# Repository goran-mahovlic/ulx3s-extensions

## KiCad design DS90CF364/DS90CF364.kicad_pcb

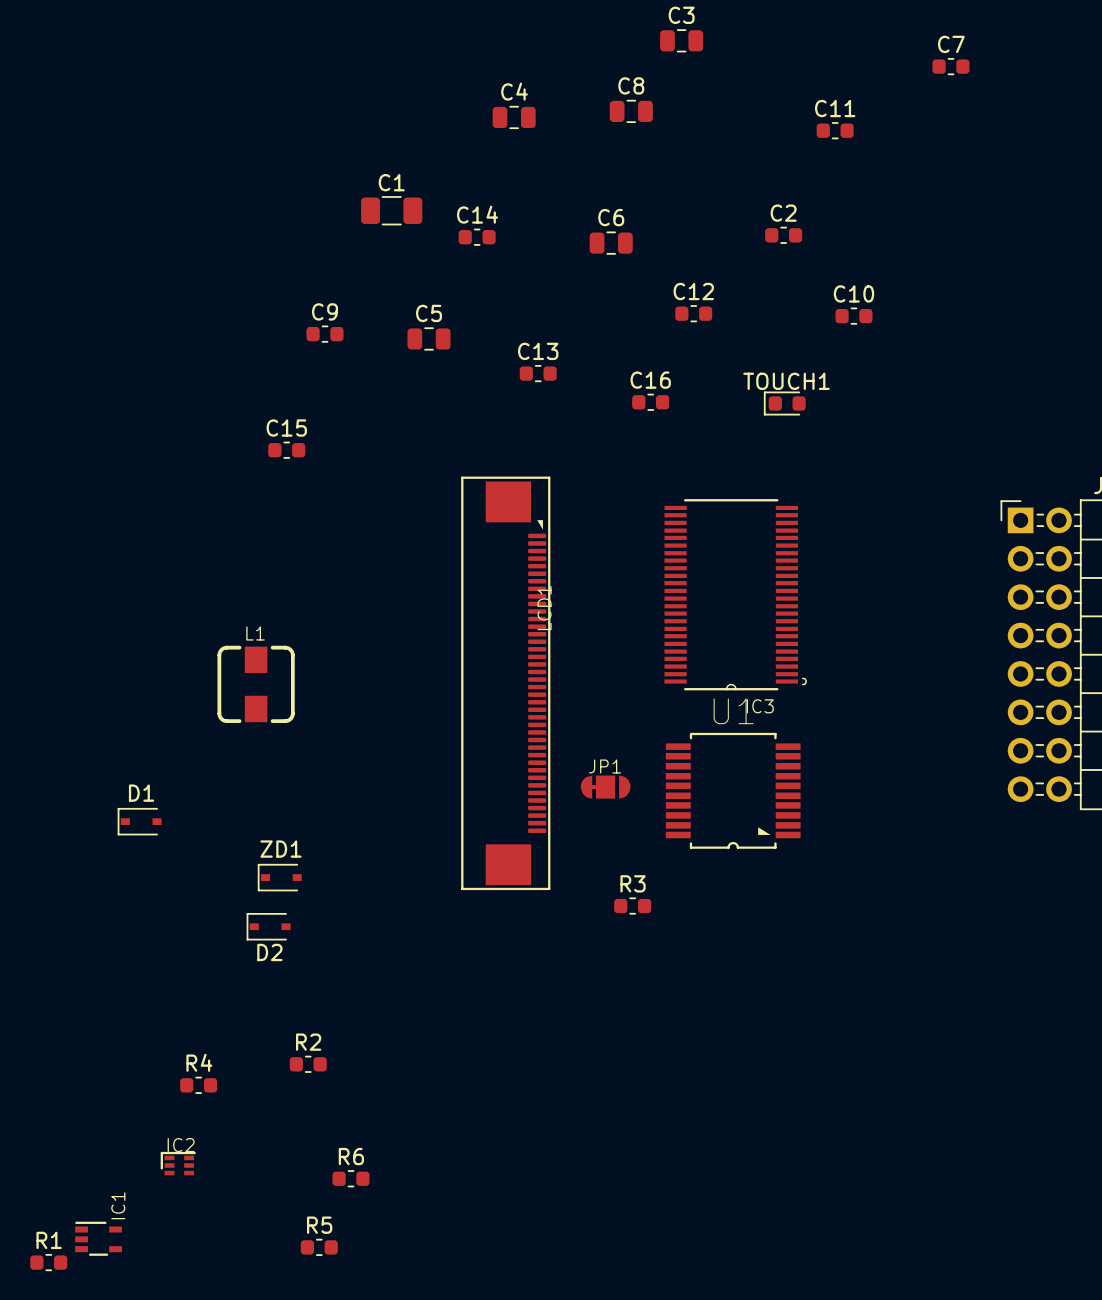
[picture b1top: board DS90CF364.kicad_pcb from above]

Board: 2 copper layers, 34 parts (0 on the bottom side), 42 nets, no tracks yet.

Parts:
C1: 4u7; C_1206_3216Metric
C2, C7, C9, C10, C11, C12, C13, C14, C15, C16: 100n; C_0603_1608Metric
C3, C8: 1u; C_0805_2012Metric
C4, C6: 10n; C_0805_2012Metric
C5: 2u2; C_0805_2012Metric
D1: D_Schottky; D_SOD-323
D2: D_Zener; D_SOD-323
IC1: TPS61169DCKR; DCK5
IC2: TPD4E001DRLR; DRL6
IC3: AR1021-I/SS; SOP65P780X200-20N
J1: Conn_02x08_Odd_Even; PinHeader_2x08_P2.54mm_Horizontal
JP1: JP3-CUT
L1: DLG-0403-4R7; DE0403
LCD1: PCA-6-LA-40-HL-3; FPC_40
R1, R2: 10R; R_0603_1608Metric
R3: 10K; R_0603_1608Metric
R4: 20K; R_0603_1608Metric
R5: 4K7; R_0603_1608Metric
R6: 1K; R_0603_1608Metric
TOUCH1: LED; LED_0603_1608Metric
U1: DS90CF364AMTD; SOP50P800X110-48N
ZD1: BZX384-B30.115; D_SOD-323

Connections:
3V3: C1.1, C2.2, C5.1, C7.2, C8.2, C9.1, C10.1, C11.1, C12.1, C13.1, C14.1, C15.1, C16.1, IC2.6, IC3.1, J1.1, J1.2, L1.1, LCD1.4, R1.1, R3.2, R6.2, U1.12, U1.20, U1.28, U1.36, U1.42, U1.48
/LCD_DISP: LCD1.31, R3.1
/LTDC_CLK: LCD1.30, U1.23
/LTDC_DE: LCD1.34, U1.5
/LTDC_HSYNC: LCD1.32, U1.2
/LTDC_RESET: JP1.COM, LCD1.36
/LTDC_VSYNC: LCD1.33, U1.4
/Touch_XL: C6.1, IC2.4, IC3.19, LCD1.39, R4.2
/Touch_XR: IC2.1, IC3.18, LCD1.37
/Touch_YD: C4.1, IC2.2, IC3.16, LCD1.38
/Touch_YU: IC2.5, IC3.15, LCD1.40
/VLED_SW: D1.2, IC1.1, L1.2
GN4: IC3.11, J1.13
GN5: IC3.9, J1.15
GND: C1.2, C2.1, C3.2, C4.2, C5.2, C6.2, C7.1, C8.1, C9.2, C10.2, C11.2, C12.2, C13.2, C14.2, C15.2, C16.2, IC1.2, IC2.3, IC3.2, IC3.3, IC3.4, IC3.7, IC3.14, IC3.17, IC3.20, J1.3, J1.4, JP1.NO, LCD1.3, LCD1.5, LCD1.6, LCD1.13, LCD1.14, LCD1.21, LCD1.22, LCD1.29, R2.2, TOUCH1.1, U1.3, U1.7, U1.13, U1.18, U1.19, U1.21, U1.25, U1.32, U1.38, U1.44
GP4: IC3.13, J1.14
GP5: IC1.4, J1.16
LTDC_B2: LCD1.23, U1.41
LTDC_B3: LCD1.24, U1.43
LTDC_B4: LCD1.25, U1.45
LTDC_B5: LCD1.26, U1.46
LTDC_B6: LCD1.27, U1.47
LTDC_B7: LCD1.28, U1.1
LTDC_G2: LCD1.15, U1.33
LTDC_G3: LCD1.16, U1.34
LTDC_G4: LCD1.17, U1.35
LTDC_G5: LCD1.18, U1.37
LTDC_G6: LCD1.19, U1.39
LTDC_G7: LCD1.20, U1.40
LTDC_R2: LCD1.7, U1.24
LTDC_R3: LCD1.8, U1.26
LTDC_R4: LCD1.9, U1.27
LTDC_R5: LCD1.10, U1.29
LTDC_R6: LCD1.11, U1.30
LTDC_R7: LCD1.12, U1.31
unnamed: IC1.5, R1.2
unnamed: IC3.5, R4.1
unnamed: IC3.6, R5.2
unnamed: R5.1, TOUCH1.2
unnamed: R6.1, U1.22
VLED+: C3.1, D1.1, D2.1, LCD1.2
VLED-: D2.2, IC1.3, LCD1.1, R2.1

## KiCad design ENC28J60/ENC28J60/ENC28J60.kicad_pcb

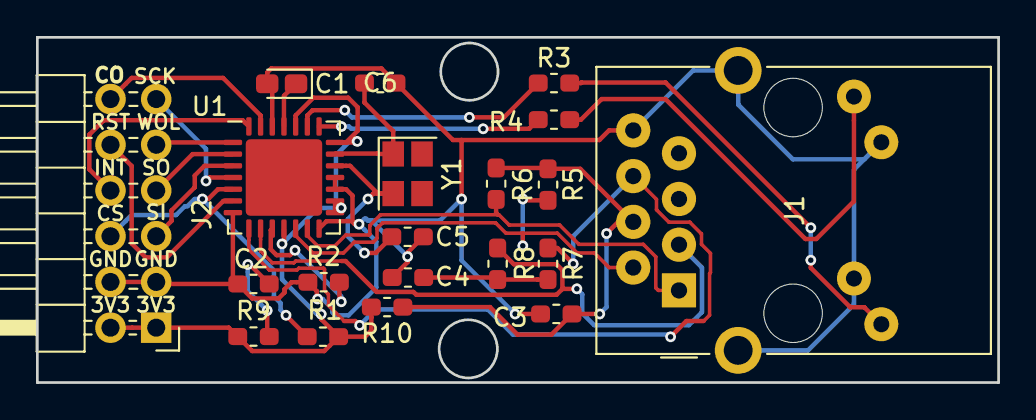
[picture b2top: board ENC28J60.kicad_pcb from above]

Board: 2 copper layers, 53.4 x 19.2 mm, 20 parts (0 on the bottom side), 25 nets.

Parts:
C1: 10u; CP_EIA-1608-08_AVX-J_Pad1.25x1.05mm_HandSolder
C2, C3, C4: 100n; C_0603_1608Metric_Pad1.05x0.95mm_HandSolder
C5, C6: 18p; C_0603_1608Metric_Pad1.05x0.95mm_HandSolder
J1: RJ45; RJ45_Amphenol_RJMG1BD3B8K1ANR
J2: Conn_02x06_Odd_Even; PinHeader_2x06_P2.54mm_Horizontal
R1, R9: 4K7; R_0603_1608Metric_Pad1.05x0.95mm_HandSolder
R2: 2K7; R_0603_1608Metric_Pad1.05x0.95mm_HandSolder
R3, R4, R5, R6, R7, R8: 270R; R_0603_1608Metric_Pad1.05x0.95mm_HandSolder
R10: 10R; R_0603_1608Metric_Pad1.05x0.95mm_HandSolder
U1: ENC28J60; QFN-28-1EP_6x6mm_P0.65mm_EP4.25x4.25mm
Y1: Crystal; Crystal_SMD_SeikoEpson_FA238-4Pin_3.2x2.5mm

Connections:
+3V3: J2.1, J2.2, R1.1, R9.1, R10.2, U1.11, U1.15, U1.16, U1.21, U1.24
CLKOUT: J2.12, U1.27
CS: J2.6, R1.2, U1.5
GND: C1.2, C2.2, C3.1, C4.1, C5.2, C6.2, J1.13, J1.L2, J1.L3, J1.R8, J2.3, J2.4, R2.1, U1.7, U1.14, U1.17, U1.18, U1.26
INT: J2.8, U1.28
LEDA: R3.1, U1.23
LEDB: R4.1, U1.22
unnamed: C1.1, U1.25
unnamed: C2.1, R9.2
unnamed: C3.2, J1.R4, R5.2, R6.2, R10.1
unnamed: C4.2, R7.2, R8.2
unnamed: C5.1, U1.19, Y1.2
unnamed: C6.1, U1.20, Y1.1
unnamed: J1.L1, R4.2
unnamed: J1.L4, R3.2
unnamed: R2.2, U1.10
RESET: J2.10, U1.6
SCK: J2.11, U1.4
SI: J2.5, U1.3
SO: J2.7, U1.2
TPIN+: J1.R3, R8.1, U1.9
TPIN-: J1.R6, R7.1, U1.8
TPOUT+: J1.R1, R6.1, U1.13
TPOUT-: J1.R2, R5.1, U1.12
WOL: J2.9, U1.1

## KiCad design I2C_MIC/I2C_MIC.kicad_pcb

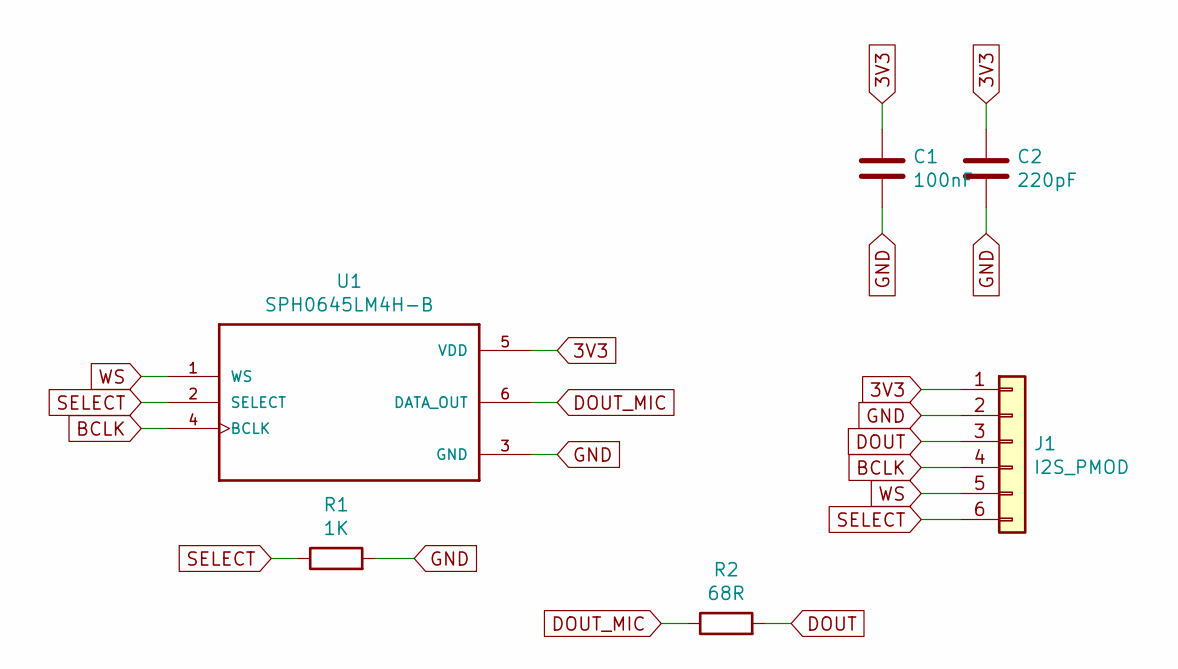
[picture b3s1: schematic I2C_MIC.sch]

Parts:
C1: 100nF; C_0603_1608Metric_Pad1.05x0.95mm_HandSolder
C2: 220pF; C_0603_1608Metric_Pad1.05x0.95mm_HandSolder
J1: I2S_PMOD; PinHeader_1x06_P2.54mm_Horizontal
R1: 1K; R_0603_1608Metric_Pad1.05x0.95mm_HandSolder
R2: 68R; R_0603_1608Metric_Pad1.05x0.95mm_HandSolder
U1: SPH0645LM4H-B; MIC_SPH0645LM4H-B

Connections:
3V3: C1.1, C2.1, J1.1, U1.5 (VDD)
BCLK: J1.4, U1.4 (BCLK)
DOUT: J1.3, R2.2
DOUT_MIC: R2.1, U1.6 (DATA_OUT)
GND: C1.2, C2.2, J1.2, R1.2, U1.3 (GND)
SELECT: J1.6, R1.1, U1.2 (SELECT)
WS: J1.5, U1.1 (WS)

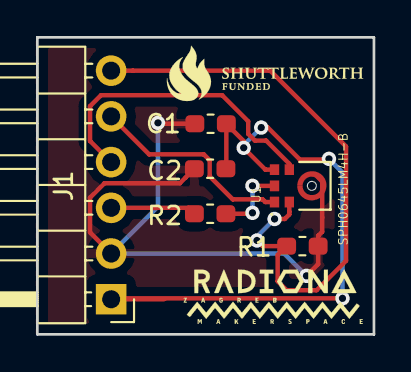
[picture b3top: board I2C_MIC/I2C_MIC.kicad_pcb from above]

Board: 2 copper layers, 18.7 x 16.5 mm, 6 parts (0 on the bottom side), 7 nets.

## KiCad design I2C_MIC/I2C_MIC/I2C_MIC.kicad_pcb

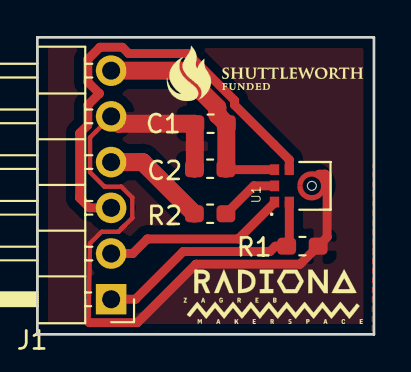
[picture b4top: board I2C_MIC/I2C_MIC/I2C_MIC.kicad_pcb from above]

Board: 2 copper layers, 18.7 x 16.5 mm, 6 parts (0 on the bottom side), 7 nets.

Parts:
C1: 100nF; C_0603_1608Metric_Pad1.05x0.95mm_HandSolder
C2: 220pF; C_0603_1608Metric_Pad1.05x0.95mm_HandSolder
J1: I2S_PMOD; PinHeader_1x06_P2.54mm_Horizontal
R1: 1K; R_0603_1608Metric_Pad1.05x0.95mm_HandSolder
R2: 68R; R_0603_1608Metric_Pad1.05x0.95mm_HandSolder
U1: MIC_SPH0645LM4H-B

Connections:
3V3: C1.1, C2.1, J1.6, U1.5
BCLK: J1.3, U1.4
DOUT: J1.4, R2.2
DOUT_MIC: R2.1, U1.6
GND: C1.2, C2.2, J1.5, R1.2, U1.3
SELECT: J1.1, R1.1, U1.2
WS: J1.2, U1.1

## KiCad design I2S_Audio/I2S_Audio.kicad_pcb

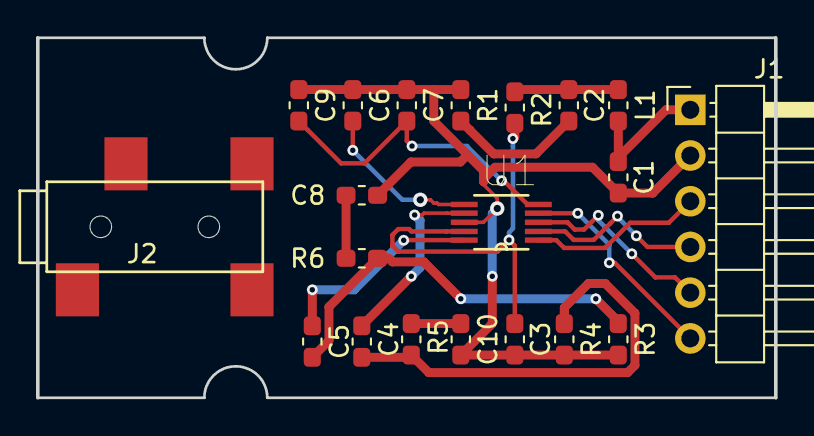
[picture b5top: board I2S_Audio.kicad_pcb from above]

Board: 2 copper layers, 41.0 x 20.0 mm, 20 parts (0 on the bottom side), 17 nets.

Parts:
C1, C3, C7: 100nF; C_0603_1608Metric_Pad1.05x0.95mm_HandSolder
C2: 4.7uF; C_0603_1608Metric_Pad1.05x0.95mm_HandSolder
C4, C5: 3.3uF; C_0603_1608Metric_Pad1.05x0.95mm_HandSolder
C6, C9: 10uF; C_0603_1608Metric_Pad1.05x0.95mm_HandSolder
C8, C10: 2.7nF; C_0603_1608Metric_Pad1.05x0.95mm_HandSolder
J1: PMOD; PinHeader_1x06_P2.54mm_Horizontal
J2: AudioJack3_Ground; audio-jack
L1: 600; L_0603_1608Metric_Pad1.05x0.95mm_HandSolder
R1: 1R/1%; R_0603_1608Metric_Pad1.05x0.95mm_HandSolder
R2: R; R_0603_1608Metric_Pad1.05x0.95mm_HandSolder
R3, R4: 10K; R_0603_1608Metric_Pad1.05x0.95mm_HandSolder
R5, R6: R470; R_0603_1608Metric_Pad1.05x0.95mm_HandSolder
U1: CS4344-CZZ; SOP50P490X110-10N

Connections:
3V3: C1.1, J1.1, L1.1
GND: C1.2, C3.2, C6.2, C7.2, C8.2, C9.2, C10.2, J1.2, R1.2, R3.1, R4.1, U1.8
LRCK: J1.5, U1.3
MCLK: J1.6, U1.4
unnamed: C2.1, L1.2, R2.2
unnamed: C2.2, R1.1
unnamed: C3.1, R2.1, U1.9
unnamed: C4.1, R4.2, R5.2
unnamed: C4.2, U1.7
unnamed: C5.1, R3.2, R6.2
unnamed: C5.2, U1.10
unnamed: C6.1, U1.6
unnamed: C7.1, C9.1, U1.5
unnamed: C8.1, R6.1
unnamed: C10.1, R5.1
SCLK: J1.4, U1.2
SDIN: J1.3, U1.1

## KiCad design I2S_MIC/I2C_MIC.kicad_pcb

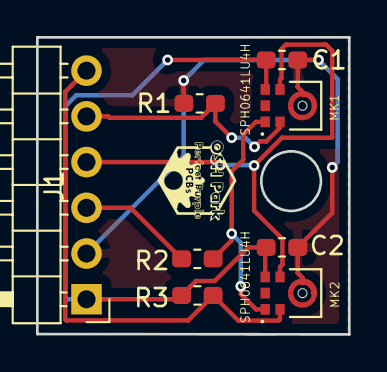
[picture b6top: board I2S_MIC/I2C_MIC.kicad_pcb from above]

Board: 2 copper layers, 17.3 x 16.5 mm, 8 parts (0 on the bottom side), 7 nets.

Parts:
C1: 100nF; C_0603_1608Metric_Pad1.05x0.95mm_HandSolder
C2: 220pF; C_0603_1608Metric_Pad1.05x0.95mm_HandSolder
J1: I2S_PMOD; PinHeader_1x06_P2.54mm_Horizontal
MK1, MK2: SPH0641LU4H; MIC_SPH0645LM4H-B
R1, R3: 1K; R_0603_1608Metric_Pad1.05x0.95mm_HandSolder
R2: 68R; R_0603_1608Metric_Pad1.05x0.95mm_HandSolder

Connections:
3V3: C1.1, C2.1, J1.1, MK1.5, MK2.5, R3.2
CLK_IN: J1.4, MK1.4, MK2.4
DOUT: J1.3, R2.2
DOUT_MIC: MK1.1, MK2.1, R2.1
GND: C1.2, C2.2, J1.2, MK1.3, MK2.3, R1.2
SELECT_L: J1.5, MK1.2, R1.1
SELECT_R: J1.6, MK2.2, R3.1
